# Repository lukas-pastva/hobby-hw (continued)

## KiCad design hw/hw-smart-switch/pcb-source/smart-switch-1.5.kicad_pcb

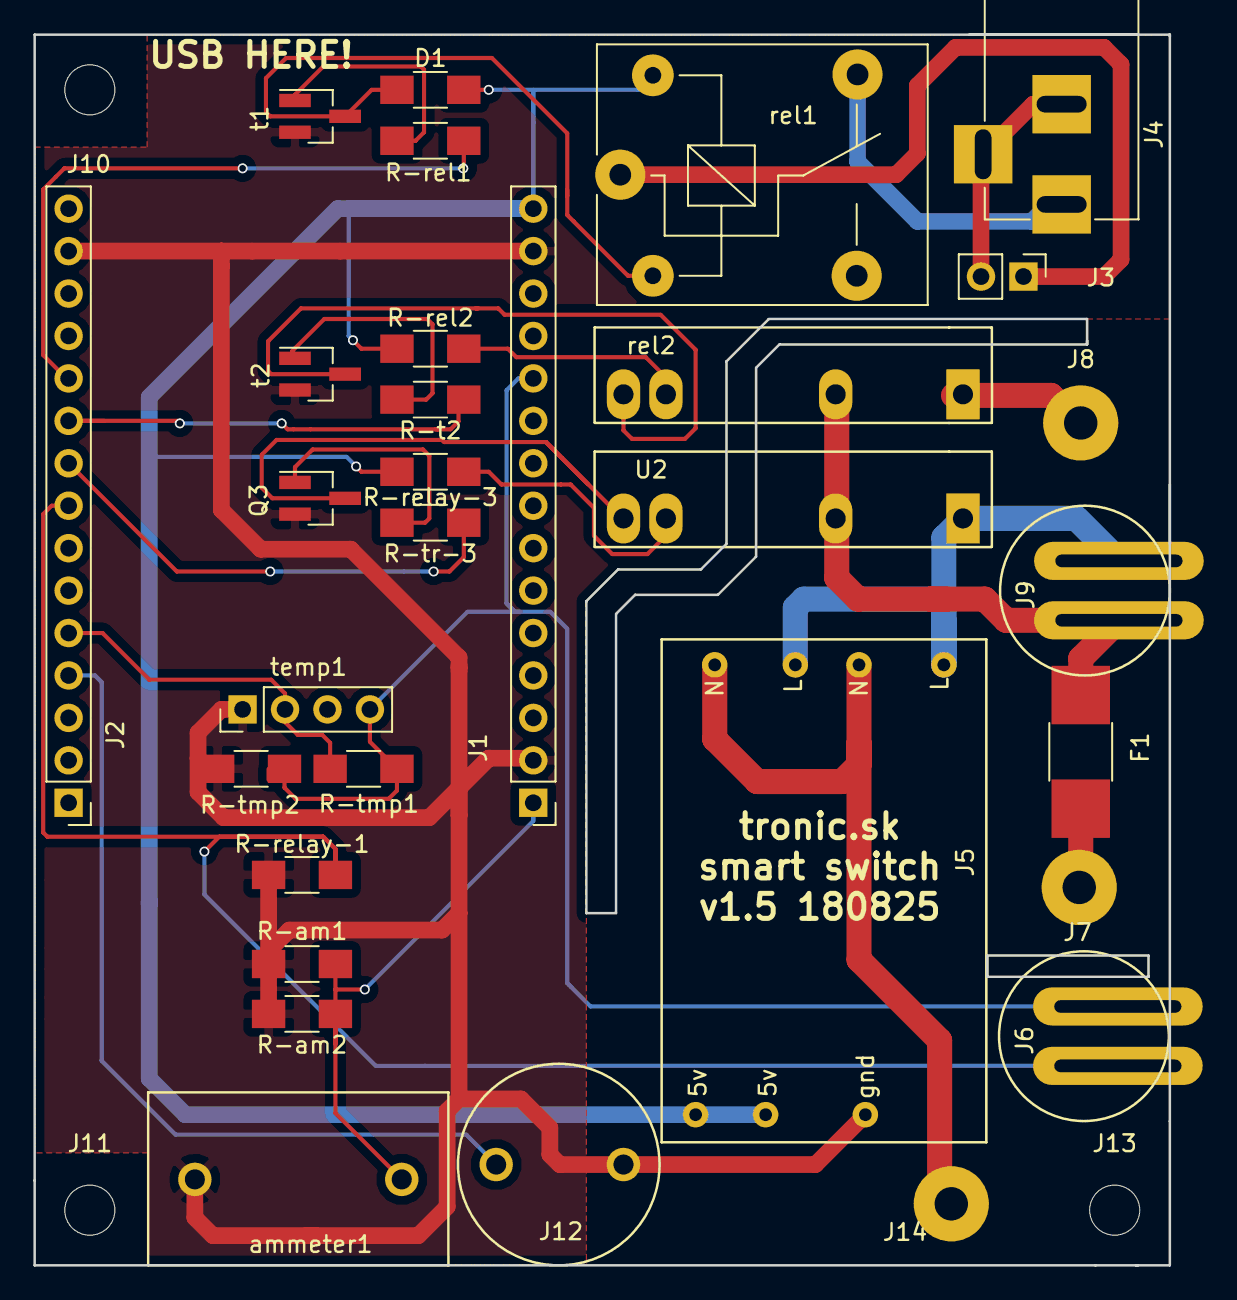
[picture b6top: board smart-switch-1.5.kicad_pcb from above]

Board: 2 copper layers, 67.9 x 73.7 mm, 34 parts (0 on the bottom side), 26 nets.

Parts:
D1: D; R_1206_HandSoldering
F1: F240V; R_1812_HandSoldering
J1: nodemcu-left; Pin_Header_Straight_1x15_Pitch2.54mm
J2: nodemcu-right; Pin_Header_Straight_1x15_Pitch2.54mm
J3: fan-in; Pin_Header_Straight_1x02_Pitch2.54mm
J4: fan-out; BARREL_JACK
J5: 5v zdroj; 5v-zdroj-dual
J6: sw1; tlacitko-na-sirku
J7: mains-in-L; SolderWirePad_single_2mmDrill
J8: mains-out-L; SolderWirePad_single_2mmDrill
J9: sw2; tlacitko-na-sirku
J10, J11, J13: Conn_01x01; MountingHole_3mm
J12: piezo; psw-piezo
J14: mains-out-N; SolderWirePad_single_2mmDrill
Q3: NPN-3; SOT-23_Handsoldering
R-am1, R-am2: R; R_1206_HandSoldering
R-rel1, R-rel2: R; R_1206_HandSoldering
R-relay-1, R-relay-3: R; R_1206_HandSoldering
R-t2: R; R_1206_HandSoldering
R-tmp1, R-tmp2: R; R_1206_HandSoldering
R-tr-3: R; R_1206_HandSoldering
U2: S116S01; psw-solid-state-relay
ammeter1: amp; psw-ammeter
rel1: relay1; Relay_SPDT_SANYOU_SRD_Series_Form_C
rel2: S116S01; psw-solid-state-relay
t1: NPN-1; SOT-23_Handsoldering
t2: NPN-2; SOT-23_Handsoldering
temp1: fht; Pin_Header_Straight_1x04_Pitch2.54mm

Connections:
3v: J1.11, J6.1, R-tmp1.2, R-tmp2.2, temp1.4
240v-in: J5.1, J9.1, U2.1
240v-out: F1.2, J9.2, U2.2, rel2.2
240v-out-plug: J8.1, rel2.1
240v-plug: F1.1, J7.1
N: J5.2, J14.1
unnamed: D1.2, rel1.2, t1.3
unnamed: Q3.1, R-tr-3.2
unnamed: Q3.3, U2.4
unnamed: R-rel1.2, t1.1
unnamed: R-rel2.2, rel2.3
unnamed: R-relay-3.1, U2.3
unnamed: R-t2.2, t2.1
unnamed: rel2.4, t2.3
a0: J1.1, R-am1.1, R-am2.1, ammeter1.1
d3: J2.4, J12.1
d4: J2.5, R-tmp1.1, temp1.2
d5: J2.8, J6.2, R-relay-1.2
d6: J2.9, R-tr-3.1
d7: J2.10, R-t2.1
d8: J2.11, R-rel1.1
fan: J4.1, rel1.4
fan-gnd: J3.2, J4.2, J4.3
fan-in: J3.1, rel1.1
g: J1.2, J1.14, J2.14, J5.4, J12.2, Q3.2, R-am1.2, R-am2.2, R-relay-1.1, R-tmp2.1, ammeter1.2, t1.2, t2.2, temp1.1
vin: D1.1, J1.15, J5.3, R-rel2.1, R-relay-3.2, rel1.5

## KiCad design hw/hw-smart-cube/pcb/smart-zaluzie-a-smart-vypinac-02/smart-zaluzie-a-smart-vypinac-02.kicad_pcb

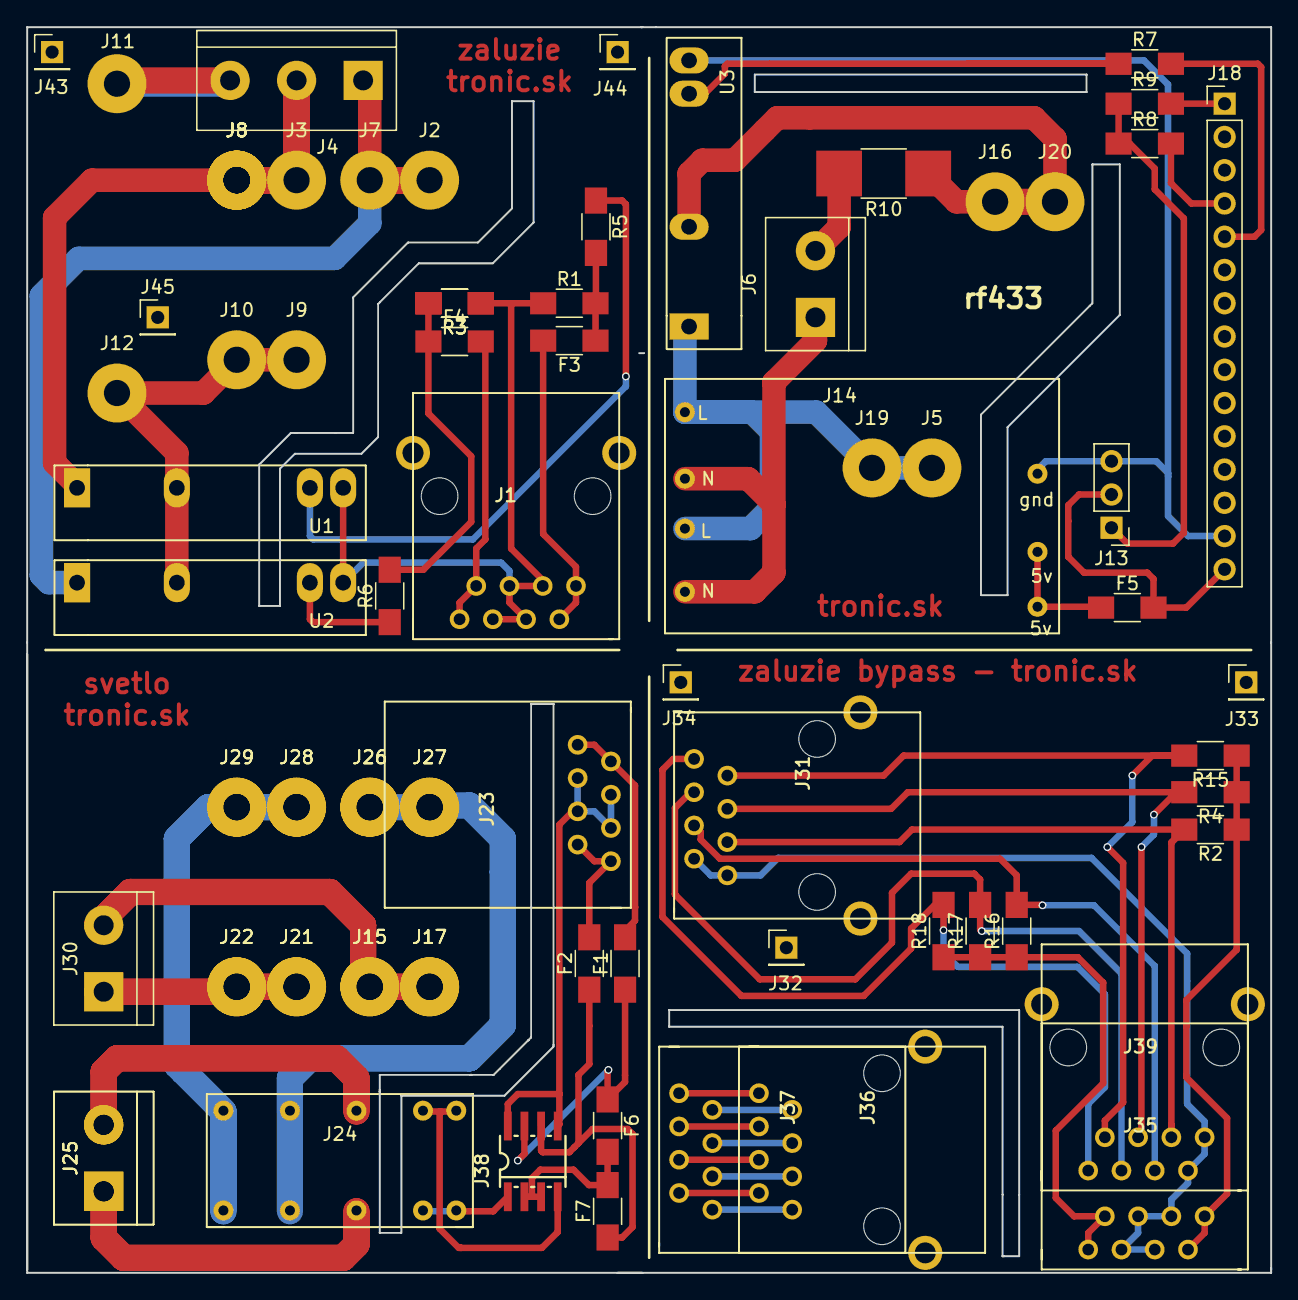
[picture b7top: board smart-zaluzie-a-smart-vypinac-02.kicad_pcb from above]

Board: 2 copper layers, 95.0 x 95.1 mm, 79 parts (0 on the bottom side), 54 nets.

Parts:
F1, F2, F3, F4, F5, F6, F7: R; R_1206_HandSoldering
J1, J31, J36, J39: RJ45; RJ45-TYCO-406549-psw
J2, J7: down-sw; SolderWirePad_single_2mmDrill
J3, J8, J8#2, J8#3, J8#4: up-sw; SolderWirePad_single_2mmDrill
J4: pwr; TerminalBlock_bornier-3_P5.08mm
J5, J19: 240v-out; SolderWirePad_single_2mmDrill
J6, J25, J25#2, J30: pws; TerminalBlock_bornier-2_P5.08mm
J9, J10: 240v; SolderWirePad_single_2mmDrill
J11: f1; SolderWirePad_single_2mmDrill
J12: f2; SolderWirePad_single_2mmDrill
J13: rf433; Pin_Header_Straight_1x03_Pitch2.54mm
J14: zdroj; 5v-zdroj-dual
J15, J15#2, J17, J17#2: up-o; SolderWirePad_single_2mmDrill
J16, J20: 240v-in; SolderWirePad_single_2mmDrill
J18: nano; Pin_Header_Straight_1x15_Pitch2.54mm
J21, J21#2, J22, J22#2: down-o; SolderWirePad_single_2mmDrill
J23, J35, J37: RJ45; psw-rj-45-no-holes
J24: relay; relay-HFD2-psw
J26, J26#2, J27, J27#2: up; SolderWirePad_single_2mmDrill
J28, J28#2, J29, J29#2: down; SolderWirePad_single_2mmDrill
J32, J33, J34, J43, J44, J45: Conn_01x01; Pin_Header_Straight_1x01_Pitch2.54mm
J38: H-bridge; 8
R1, R2, R3, R3#2, R4, R5, R6, R7, R8, R9, R15, R16, R17, R18: R; R_1206_HandSoldering
R10: R; R_1812_HandSoldering
U1, U2, U3: S116S01; psw-solid-state-relay

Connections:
2-5v: F5.2, J13.2, J18.15
2-5v-in: F5.1, J14.3
2-240in: J16.1, J20.1, R10.1, U3.2
2-240in-mains: J6.2, R10.2
2-240out: J5.1, J14.1, J19.1, U3.1
2-a0: J18.4, R8.2
2-a1: J18.5, R7.2
2-d13: J18.1, R9.2
2-gnd: J13.3, J14.4, J18.14, U3.4
2-n: J6.1, J14.2
2-rd-data: J13.1, R8.1, R9.1
3-5v-down: F2.1, F7.1, J38.6
3-5v-down-in: F2.2, J23.7, J23.8
3-5v-up: F1.1, F6.1, J38.7
3-5v-up-in: F1.2, J23.1, J23.2
3-down: J24.5, J24.10, J28.1, J28#2.1, J29.1, J29#2.1
3-down-in: J24.3, J25.1, J25#2.1
3-down-out: J21.1, J21#2.1, J22.1, J22#2.1, J30.1
3-gnd: J23.3, J23.4, J23.5, J23.6, J38.5, J38.8
3-minus: J24.6, J24.7, J38.4
3-plus: J24.1, J24.2, J38.1
3-up: J24.4, J24.9, J26.1, J26#2.1, J27.1, J27#2.1
3-up-in: J24.8, J25.2, J25#2.2
3-up-out: J15.1, J15#2.1, J17.1, J17#2.1, J30.2
5v-down: F4.1, R3.2, R3#2.2, R6.2
5v-down-in: F4.2, J1.7, J1.8
5v-up: F3.1, R1.2, R5.2
5v-up-in: F3.2, J1.1, J1.2
240v: J9.1, J10.1, J12.1, U1.2, U2.2
240v-input: J4.3, J11.1
unnamed: F6.2, F7.2, J38.2, J38.3
unnamed: R5.1, U1.3
unnamed: R6.1, U2.3
unnamed: R7.1, U3.3
down: J2.1, J4.1, J7.1, U2.1
eth-bypass-1: J36.1, J37.1
eth-bypass-2: J36.2, J37.2
eth-bypass-3: J36.3, J37.3
eth-bypass-4: J36.4, J37.4
eth-bypass-5: J36.5, J37.5
eth-bypass-6: J36.6, J37.6
eth-bypass-7: J36.7, J37.7
eth-bypass-8: J36.8, J37.8
gnd: J1.3, J1.4, J1.5, J1.6, R1.1, R3.1, R3#2.1, U1.4, U2.4
up: J3.1, J4.2, J8.1, J8#2.1, J8#3.1, J8#4.1, U1.1
zaluzia-1-down: J31.4, J39.4, R16.2
zaluzia-1-up: J31.3, J39.3, R2.2
zaluzia-2-down: J31.6, J39.6, R17.2
zaluzia-2-up: J31.5, J39.5, R4.2
zaluzia-3-down: J31.8, J39.8, R18.2
zaluzia-3-up: J31.7, J39.7, R15.2
zaluzia-minus: J31.1, J31.2, J35.3, J35.4, J35.5, J35.6, J39.1, J39.2
zaluzia-out-down: J35.7, J35.8, R16.1, R17.1, R18.1
zaluzia-out-up: J35.1, J35.2, R2.1, R4.1, R15.1

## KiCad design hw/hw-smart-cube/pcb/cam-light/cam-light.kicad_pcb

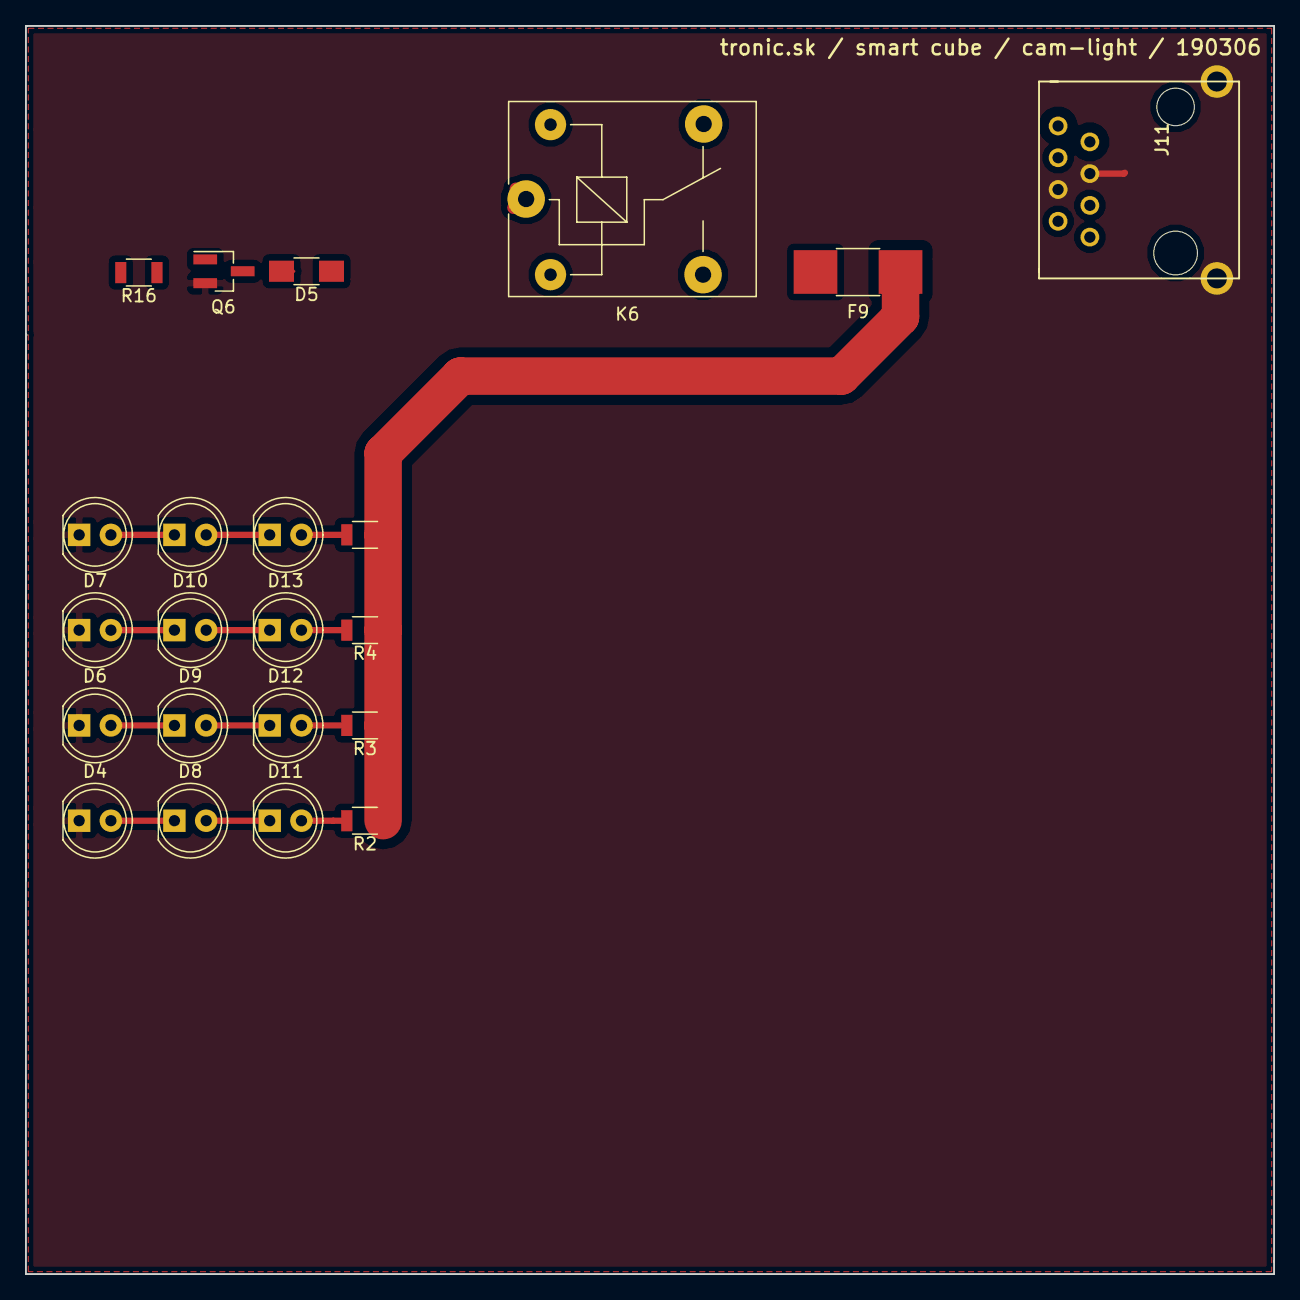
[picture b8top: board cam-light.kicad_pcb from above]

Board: 2 copper layers, 99.8 x 99.8 mm, 22 parts (0 on the bottom side), 18 nets.

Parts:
D1, D2, D3, D4, D6, D7, D8, D9, D10, D11, D12, D13: LED; LED_D5.0mm
D5: D; R_1206_HandSoldering
F9: fuse1; L_1812_HandSoldering
J11: net; psw-rj45-190128
K6: relay; Relay_SPDT_SANYOU_SRD_Series_Form_C
Q6: T; SOT-23_Handsoldering
R1, R2, R3, R4, R16: R; R_1206

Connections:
12V: D5.1, K6.1, K6.5
unnamed: D1.2, D2.1
unnamed: D2.2, D3.1
unnamed: D3.2, R1.2
unnamed: D4.2, D8.1
unnamed: D5.2, K6.2, Q6.3
unnamed: D6.2, D9.1
unnamed: D7.2, D10.1
unnamed: D10.2, D13.1
unnamed: D8.2, D11.1
unnamed: D11.2, R2.2
unnamed: D9.2, D12.1
unnamed: D12.2, R3.2
unnamed: D13.2, R4.2
unnamed: Q6.1, R16.1
gnd: D1.1, D4.1, D6.1, D7.1, J11.4, J11.5, J11.9, Q6.2
r-out: F9.1, J11.7, J11.8, R1.1, R2.1, R3.1, R4.1
r-out1: F9.2, K6.4
